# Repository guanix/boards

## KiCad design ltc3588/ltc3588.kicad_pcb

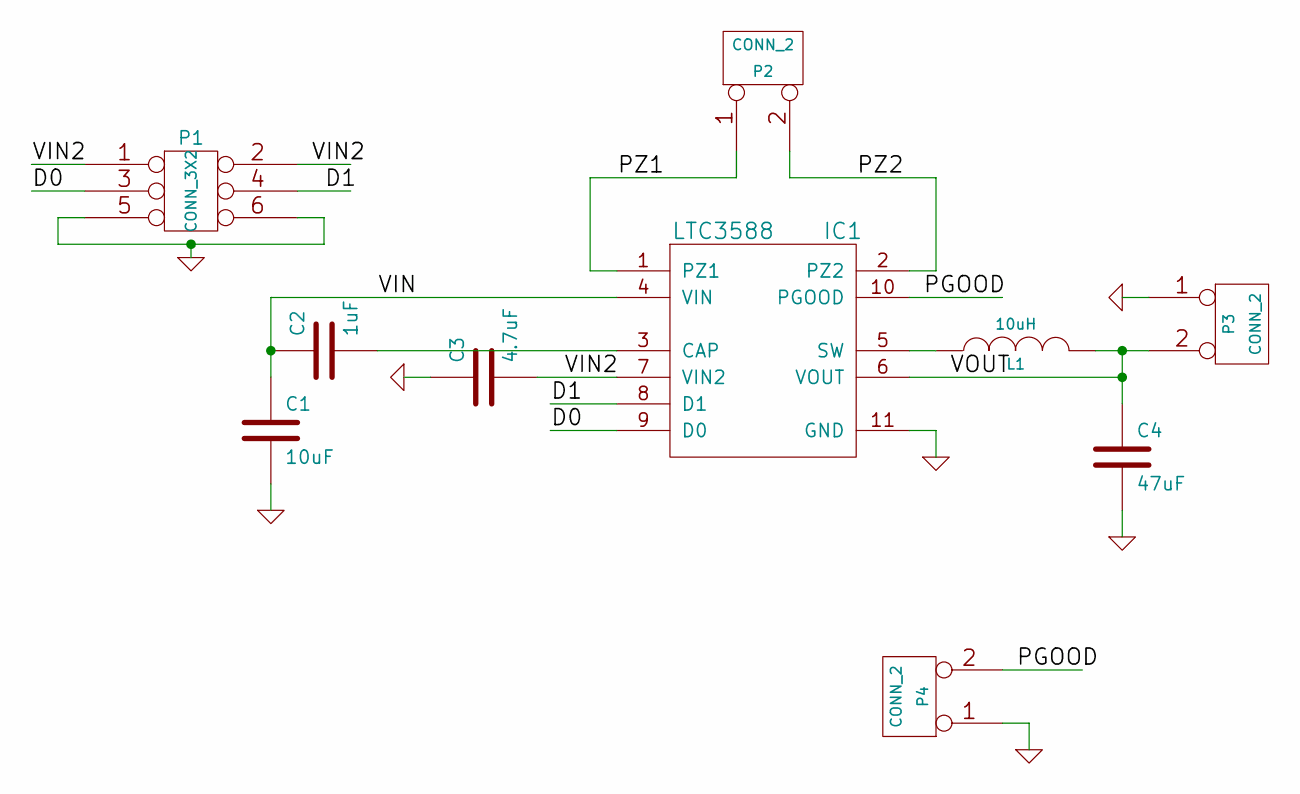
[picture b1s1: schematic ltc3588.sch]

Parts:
C1: 10uF
C2: 1uF
C3: 4.7uF
C4: 47uF
IC1: LTC3588
L1: 10uH
P1: CONN_3X2
P2, P3, P4: CONN_2

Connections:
/D0: IC1.9 (D0), P1.3
/D1: IC1.8 (D1), P1.4
/PGOOD: IC1.10 (PGOOD), P4.2 (PM)
/PZ1: IC1.1 (PZ1), P2.1
/PZ2: IC1.2 (PZ2), P2.2 (PM)
/VIN: C1.1, C2.1, IC1.4 (VIN)
/VIN2: C3.2, IC1.7 (VIN2), P1.1, P1.2
/VOUT: C4.1, IC1.6 (VOUT), L1.2, P3.2 (PM)
GND: C1.2, C3.1, C4.2, IC1.11 (GND), P1.5, P1.6, P3.1, P4.1
unnamed: IC1.5 (SW), L1.1
unnamed: C2.2, IC1.3 (CAP)

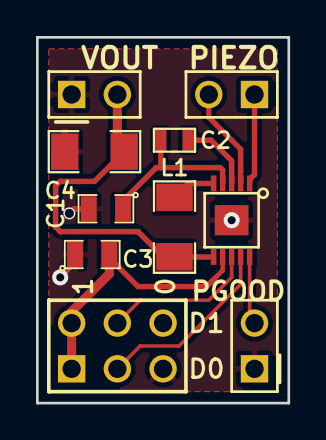
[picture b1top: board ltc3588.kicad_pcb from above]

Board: 2 copper layers, 14.0 x 20.3 mm, 10 parts (0 on the bottom side), 11 nets.

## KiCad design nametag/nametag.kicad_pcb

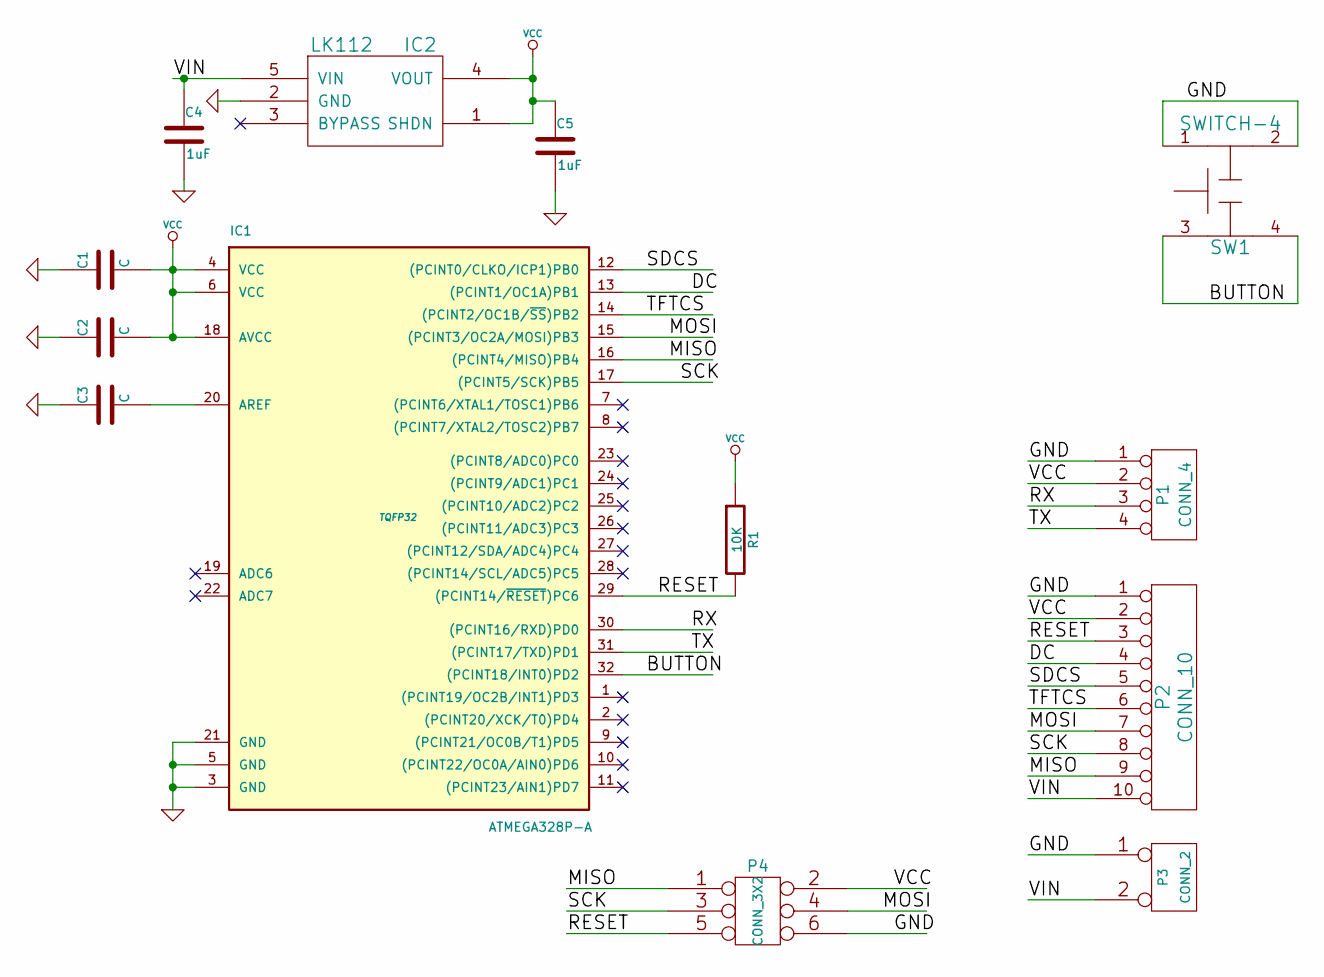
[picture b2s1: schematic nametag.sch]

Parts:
C1, C2, C3: C
C4, C5: 1uF
IC1: ATMEGA328P-A; TQFP32
IC2: LK112
P1: CONN_4
P2: CONN_10
P3: CONN_2
P4: CONN_3X2
R1: 10K
SW1: SWITCH-4

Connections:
/BUTTON: IC1.32 ((PCINT18/INT0)PD2), SW1.3, SW1.4
/DC: IC1.13 ((PCINT1/OC1A)PB1), P2.4
/MISO: IC1.16 ((PCINT4/MISO)PB4), P2.9, P4.1
/MOSI: IC1.15 ((PCINT3/OC2A/MOSI)PB3), P2.7, P4.4
/RESET: IC1.29 ((PCINT14/~RESET~)PC6), P2.3, P4.5, R1.2
/RX: IC1.30 ((PCINT16/RXD)PD0), P1.3
/SCK: IC1.17 ((PCINT5/SCK)PB5), P2.8, P4.3
/SDCS: IC1.12 ((PCINT0/CLKO/ICP1)PB0), P2.5
/TFTCS: IC1.14 ((PCINT2/OC1B/~SS~)PB2), P2.6
/TX: IC1.31 ((PCINT17/TXD)PD1), P1.4
/VIN: C4.1, IC2.5 (VIN), P2.10, P3.2 (PM)
GND: C1.1, C2.1, C3.1, C4.2, C5.2, IC1.3 (GND), IC1.5 (GND), IC1.21 (GND), IC2.2 (GND), P1.1, P2.1, P3.1, P4.6, SW1.1, SW1.2
unnamed: C3.2, IC1.20 (AREF)
VCC: C1.2, C2.2, C5.1, IC1.4 (VCC), IC1.6 (VCC), IC1.18 (AVCC), IC2.1 (SHDN), IC2.4 (VOUT), P1.2, P2.2, P4.2, R1.1

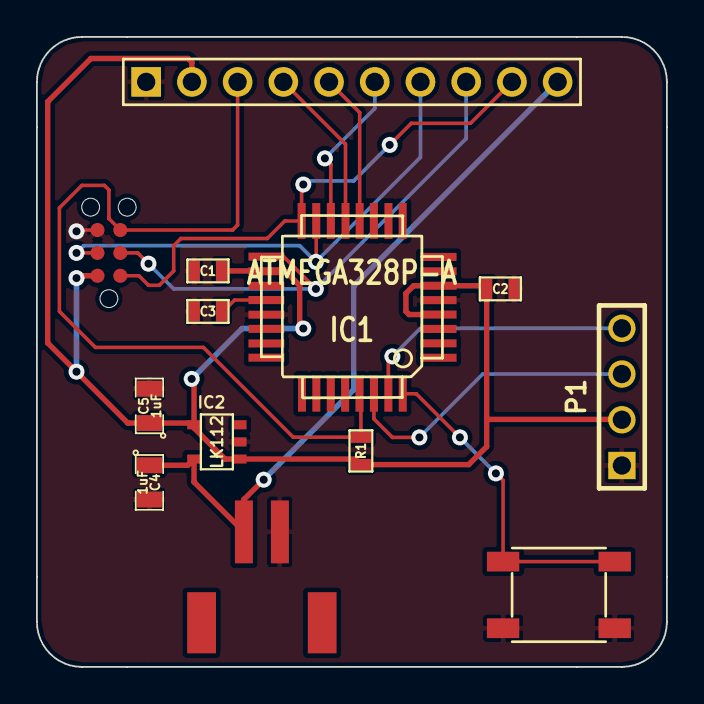
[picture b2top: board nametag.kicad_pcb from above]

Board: 2 copper layers, 35.0 x 35.0 mm, 13 parts (0 on the bottom side), 14 nets.

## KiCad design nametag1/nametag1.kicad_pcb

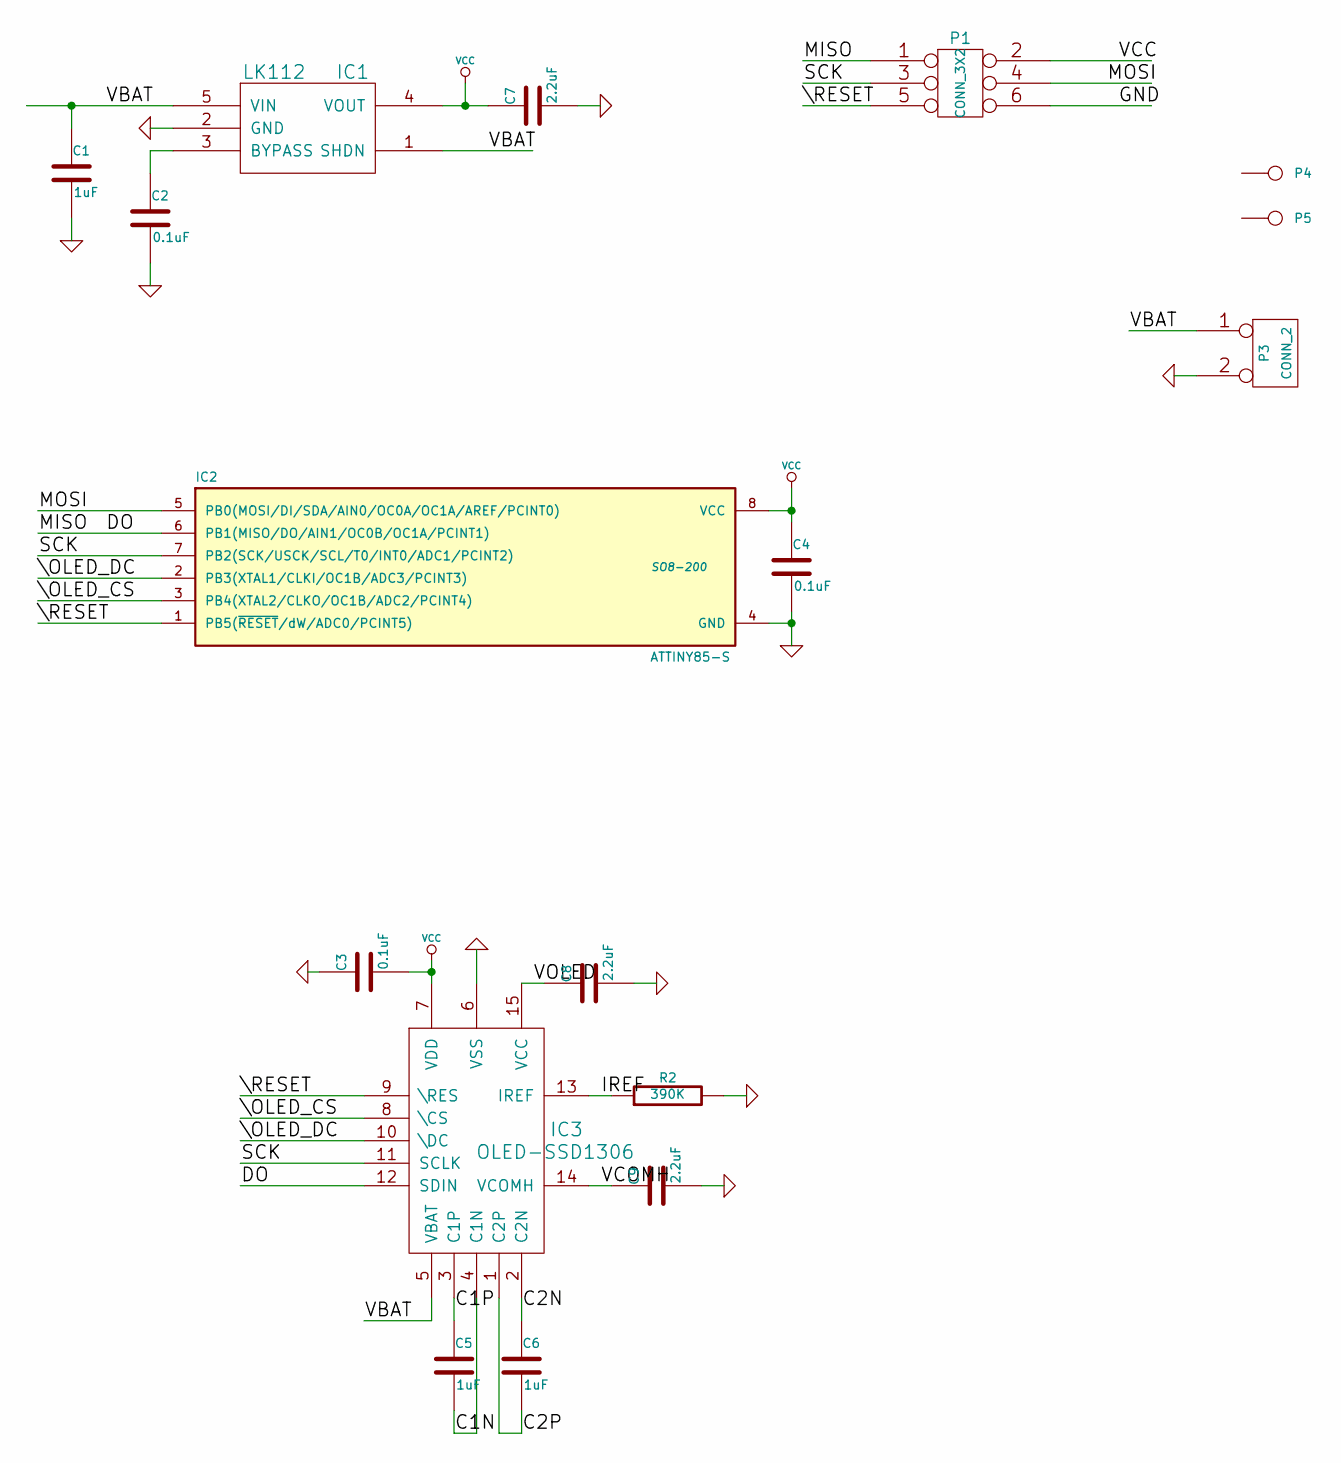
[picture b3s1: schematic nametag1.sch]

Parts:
C1, C5, C6: 1uF
C2, C3, C4: 0.1uF
C7, C8, C9: 2.2uF
IC1: LK112
IC2: ATTINY85-S; SO8-200
IC3: OLED-SSD1306
P1: CONN_3X2
P3: CONN_2
P4, P5: CONN_1
R2: 390K

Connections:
/C1N: C5.2, IC3.4 (C1N)
/C1P: C5.1, IC3.3 (C1P)
/C2N: C6.1, IC3.2 (C2N)
/C2P: C6.2, IC3.1 (C2P)
/DO: IC2.6 (PB1(MISO/DO/AIN1/OC0B/OC1A/PCINT1)), IC3.12 (SDIN), P1.1
/IREF: IC3.13 (IREF), R2.1
/MOSI: IC2.5 (PB0(MOSI/DI/SDA/AIN0/OC0A/OC1A/AREF/PCI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), P1.4
/SCK: IC2.7 (PB2(SCK/USCK/SCL/T0/INT0/ADC1/PCINT2)), IC3.11 (SCLK), P1.3
/VBAT: C1.1, IC1.1 (SHDN), IC1.5 (VIN), IC3.5 (VBAT), P3.1
/VCOMH: C9.1, IC3.14 (VCOMH)
/VOLED: C8.1, IC3.15 (VCC)
/\OLED_CS: IC2.3 (PB4(XTAL2/CLKO/OC1B/ADC2/PCINT4)), IC3.8 (\CS)
/\OLED_DC: IC2.2 (PB3(XTAL1/CLKI/OC1B/ADC3/PCINT3)), IC3.10 (\DC)
/\RESET: IC2.1 (PB5(~RESET~/dW/ADC0/PCINT5)), IC3.9 (\RES), P1.5
GND: C1.2, C2.2, C3.1, C4.2, C7.2, C8.2, C9.2, IC1.2 (GND), IC2.4 (GND), IC3.6 (VSS), P1.6, P3.2 (PM), R2.2
unnamed: C2.1, IC1.3 (BYPASS)
VCC: C3.2, C4.1, C7.1, IC1.4 (VOUT), IC2.8 (VCC), IC3.7 (VDD), P1.2

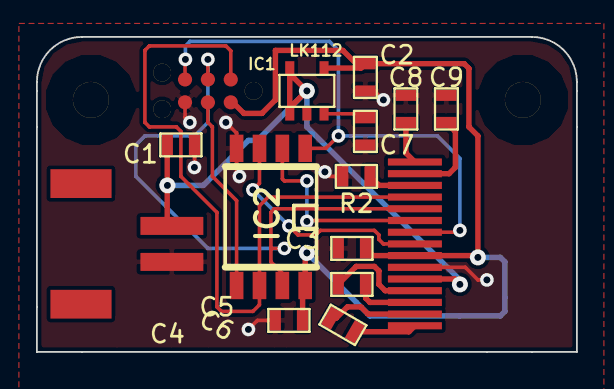
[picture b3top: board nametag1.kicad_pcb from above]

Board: 2 copper layers, 30.0 x 17.5 mm, 17 parts (0 on the bottom side), 17 nets.

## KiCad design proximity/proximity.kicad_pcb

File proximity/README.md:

# nRF51822 based Bluetooth Low Energy proximity tag and breakout board

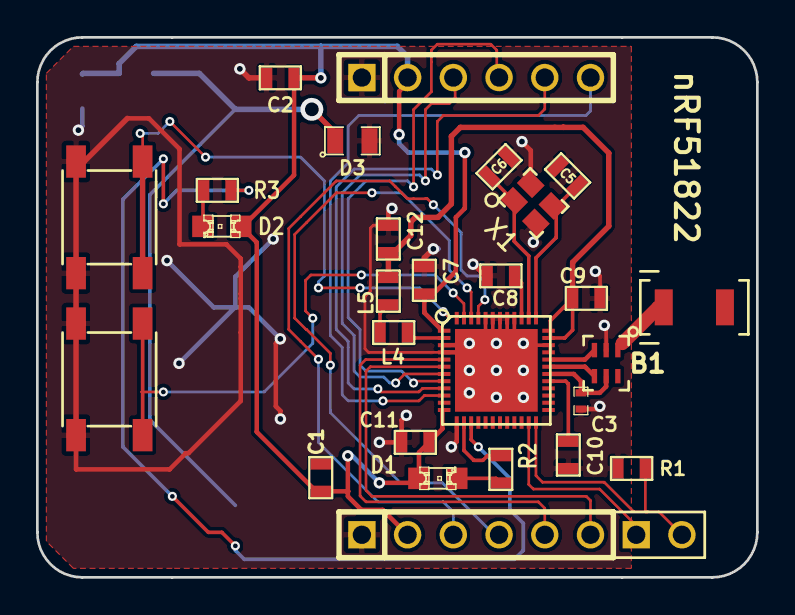
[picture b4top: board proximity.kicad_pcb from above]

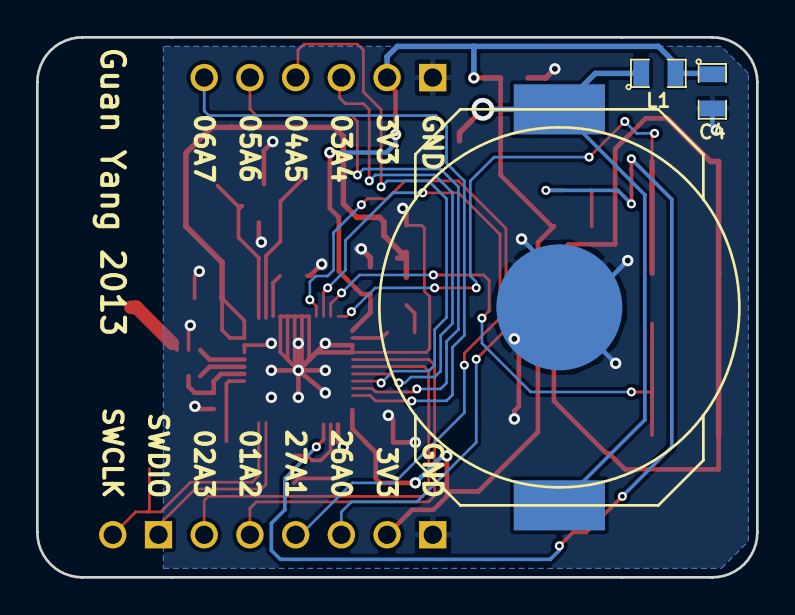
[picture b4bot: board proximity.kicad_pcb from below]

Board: 2 copper layers, 40.0 x 30.0 mm, 31 parts (3 on the bottom side), 30 nets.

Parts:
B1: BALUN-JOHANSON
BT1: BATTERY; BAT-BK912
C1, C2: 0.1uF; SM0603
C3: 2.2nF; SM0402
C4: 10uF; SM0805
C5, C6: 12pF; SM0603
C7: 4.7uF; SM0603
C8, C11: 100nF; SM0603
C9: 1nF; SM0603
C10: 47nF; SM0603
C12: 1uF; SM0603
D1, D2: LED; LED-0805
D3: DIODE; SM0805
IC1: NRF51822; QFN48+1-0.4MM-SHORTPADS
L1: INDUCTOR; SM0805
L4: 10uH; SM0603
L5: 15nH; SM0603
P1: CONN_2; PIN_ARRAY_2X1
P3: AIN_0_3; PIN_ARRAY-6X1
P4: AIN_4_7; PIN_ARRAY-6X1
R1: 12K; SM0603
R2, R3: 100R; SM0603
SW1, SW2: SWITCH-4; SWITCH-ALPS
U1: ANTENNA-NC; ANTENNA-JOHANSON-2.45GHZ
X1: NX2520SA; CRYSTAL-2520

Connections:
/AIN0: IC1.45, P3.3
/AIN1: IC1.46, P3.4
/AIN2: IC1.5, P3.5
/AIN3: IC1.6, P3.6
/AIN4: IC1.7, P4.3
/AIN5: IC1.8, P4.4
/AIN6: IC1.9, P4.5
/AIN7: IC1.10, P4.6
/ANT1: B1.4, IC1.31
/ANT2: B1.3, IC1.32
/LED1: IC1.14, R2.2
/LED2: IC1.15, R3.2
/SW1: IC1.48, SW1.3, SW1.4
/SW2: IC1.47, SW2.3, SW2.4
/SWCLK: IC1.24, P1.2, R1.1
/SWDIO: IC1.23, P1.1
/VDD_PA: B1.5, C3.1, IC1.30
AVDD: C9.1, C12.1, IC1.35, IC1.36, L5.1
GND: B1.2, BT1.2, C2.1, C3.2, C4.2, C5.1, C6.1, C7.2, C8.2, C9.2, C10.2, C11.2, C12.2, D3.2, IC1.3, IC1.4, IC1.13, IC1.33, IC1.34, IC1.40, IC1.41, IC1.42, IC1.43, IC1.44, IC1.49, P3.1, P4.1, R1.2, SW1.1, SW1.2, SW2.1, SW2.2, X1.2, X1.4
unnamed: B1.1, U1.1
unnamed: BT1.1, D3.1, L1.1
unnamed: D2.2, R3.1
unnamed: D1.2, R2.1
unnamed: C8.1, IC1.39
unnamed: IC1.2, L4.2
unnamed: L4.1, L5.2
unnamed: C10.1, IC1.29
unnamed: C5.2, IC1.37, X1.3
unnamed: C6.2, IC1.38, X1.1
VCC: C1.2, C2.2, C4.1, C7.1, C11.1, D1.1, D2.1, IC1.1, IC1.12, L1.2, P3.2, P4.2

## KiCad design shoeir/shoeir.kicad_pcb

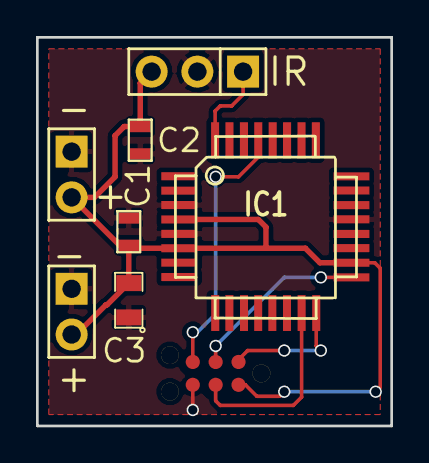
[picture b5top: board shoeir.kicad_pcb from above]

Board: 2 copper layers, 19.7 x 21.6 mm, 8 parts (0 on the bottom side), 7 nets.

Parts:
C1, C2: 0.1uF; SM0603
C3: 10uF; SM0805
IC1: ATMEGA328P-A; TQFP32
K1: CONN_3; PIN_ARRAY_3X1
P1: CONN_3X2; TC2030-MCP-NL
P2, P3: CONN_2; PIN_ARRAY_2X1

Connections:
/IR: IC1.32, K1.1
/MISO: IC1.16, P1.1
/MOSI: IC1.15, P1.4
/RESET: IC1.29, P1.5
/SCK: IC1.17, P1.3
GND: C1.2, C2.1, C3.1, IC1.3, IC1.5, IC1.21, K1.2, P1.6, P2.1, P3.1
VCC: C1.1, C2.2, C3.2, IC1.4, IC1.6, IC1.18, K1.3, P1.2, P2.2, P3.2

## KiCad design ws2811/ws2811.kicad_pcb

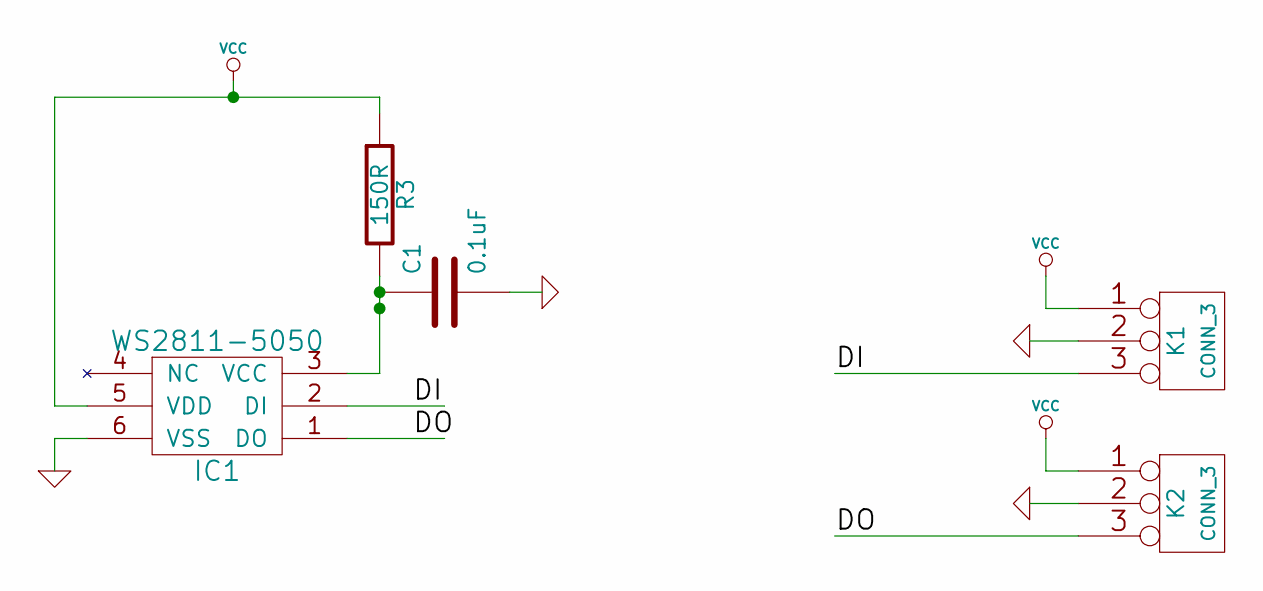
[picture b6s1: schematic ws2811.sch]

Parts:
C1: 0.1uF
IC1: WS2811-5050
K1, K2: CONN_3
R3: 150R

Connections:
/DI: IC1.2 (DI), K1.3
/DO: IC1.1 (DO), K2.3
GND: C1.2, IC1.6 (VSS), K1.2 (PM), K2.2 (PM)
unnamed: C1.1, IC1.3 (VCC), R3.2
VCC: IC1.5 (VDD), K1.1, K2.1, R3.1

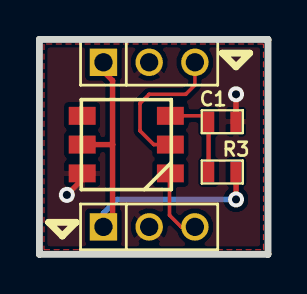
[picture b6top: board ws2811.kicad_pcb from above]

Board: 2 copper layers, 12.7 x 11.9 mm, 5 parts (0 on the bottom side), 5 nets.
